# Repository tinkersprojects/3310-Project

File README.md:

# 3310 Project
The goal of the project is to make a working Nokia 3310 that works with today's tech. The device will be as similar as the original including the screen and body (case). It is unknown what process will be in the finished device but the first will have an ESP32. The ESP32 has both Bluetooth and WiFi which will be used to connect to a smartphone as an extension accessory. 

From the Nokia 3310, the user will be able to make/receive calls and SMS/text messages as well as play original games and all other good features. Additional features like social networking will come later. A micro USB port is used for charging, programming and debugging of the ESP32.

This first prototype is very basic to see which areas would need the most amount of work and to see if this project is worth continuing. There are features missing and features that will not be apart of the device. This prototype will look mostly at getting the LCD, keypad and Bluetooth/WiFi working.

**Get involved, [contact me](https://tinkersprojects.com/contact-me/)**

**See my other projects, [https://tinkersprojects.com/](https://tinkersprojects.com/)**

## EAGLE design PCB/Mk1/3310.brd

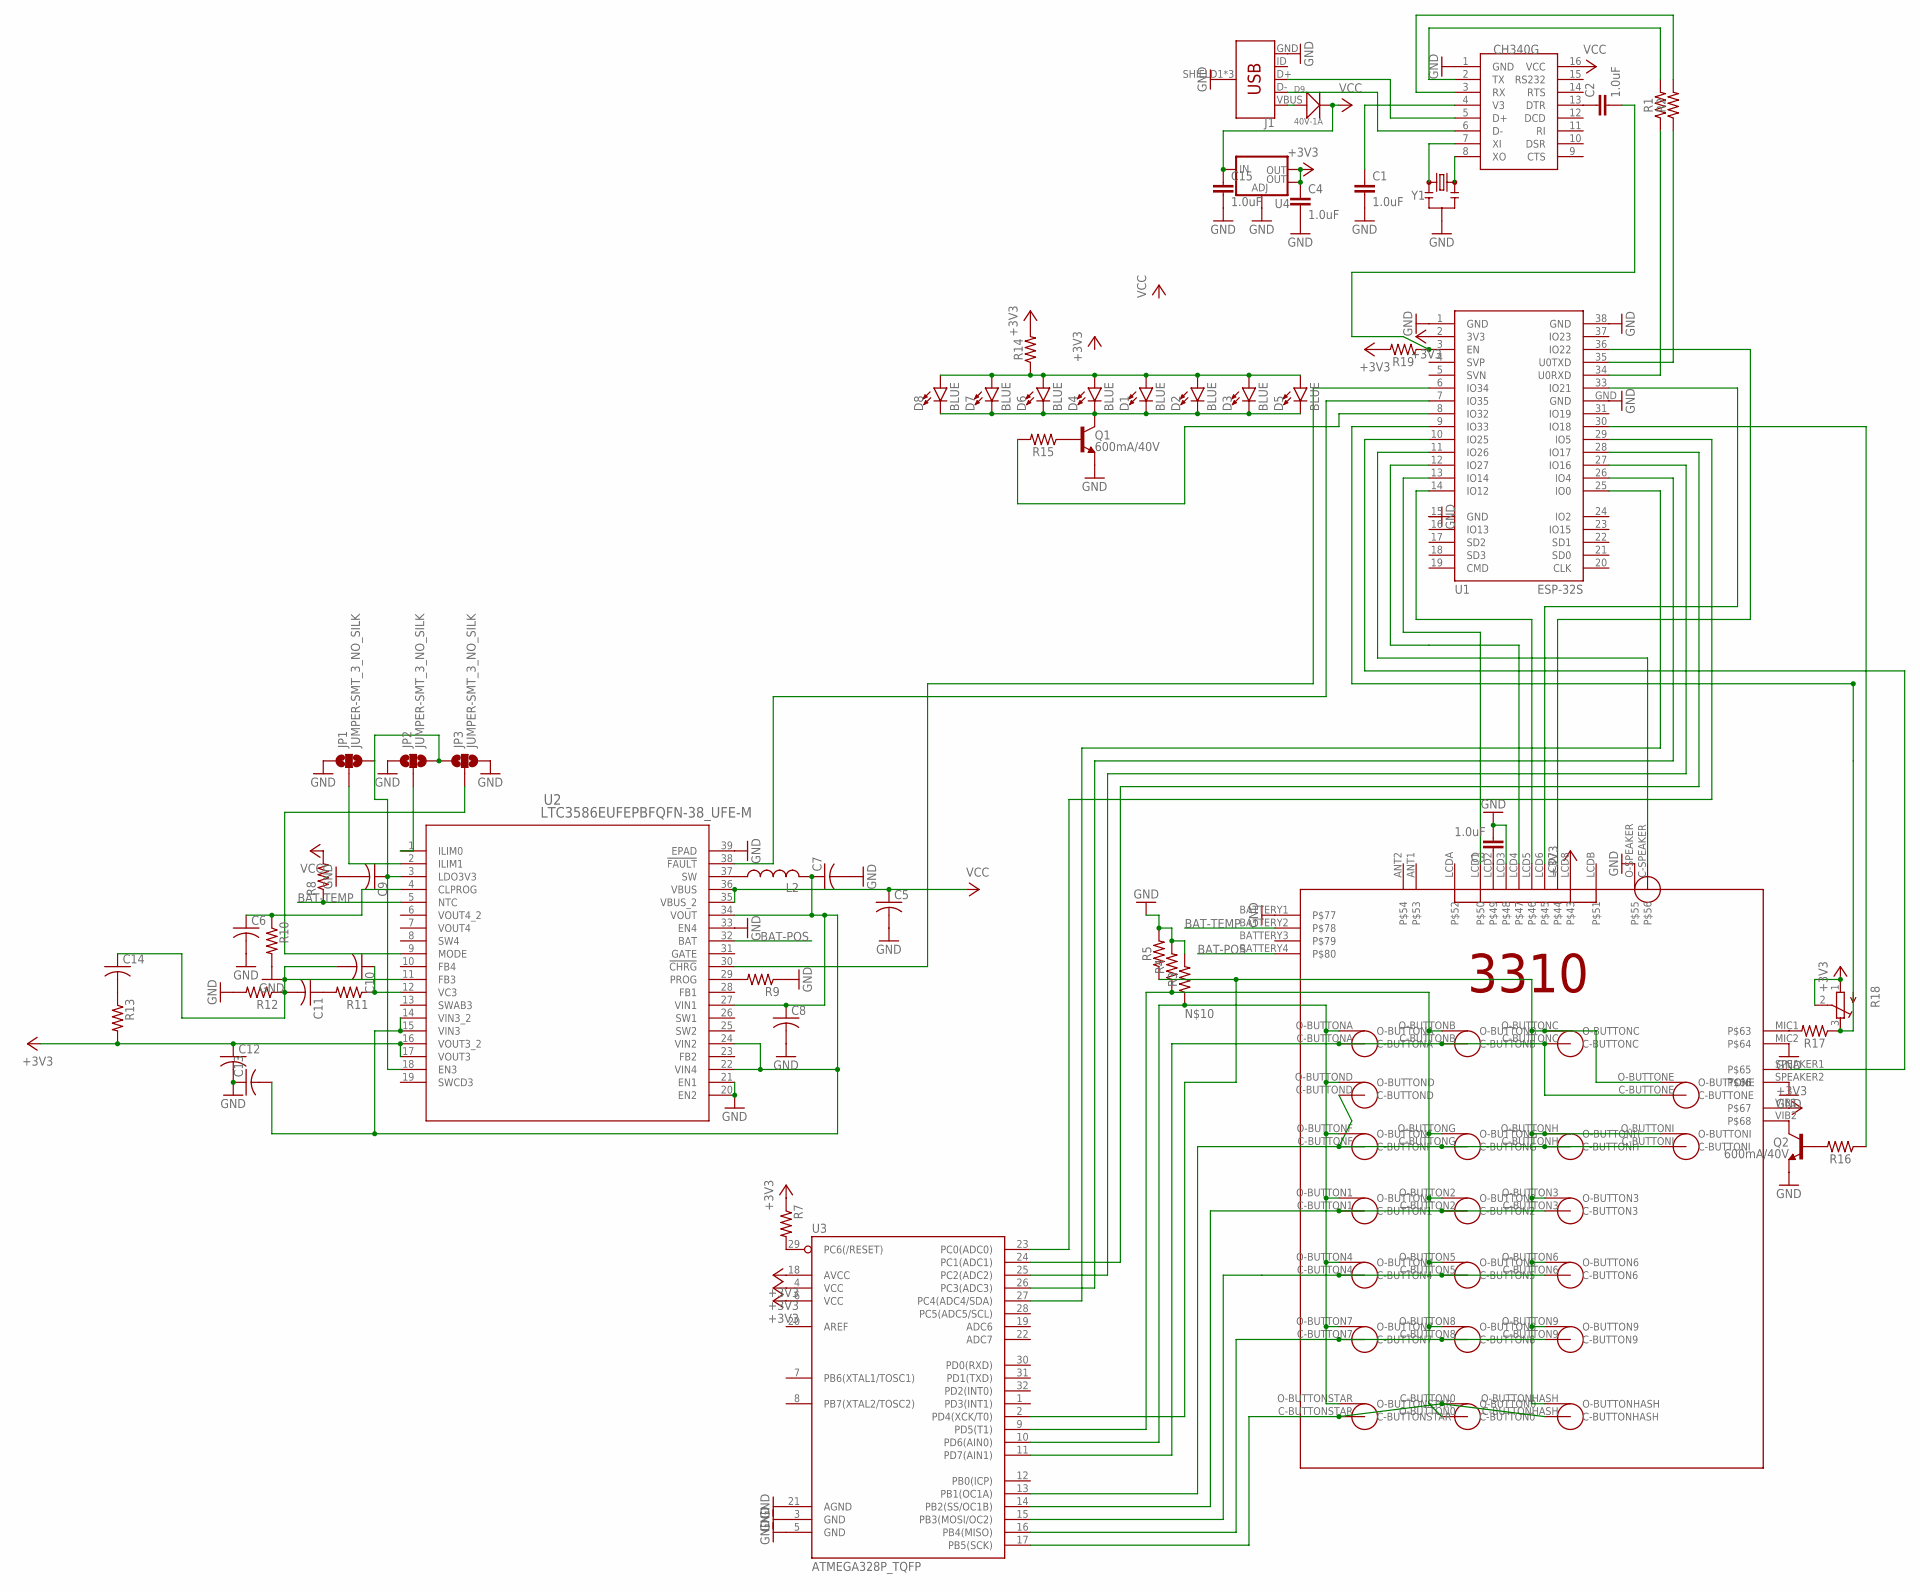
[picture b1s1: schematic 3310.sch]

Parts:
C1, C2, C3, C4, C15: 1.0uF; 0805
C5, C6, C7, C8, C9, C10, C11, C12, C13, C14: C-USC0805K; C0805K
D1, D2, D3, D4, D5, D6, D7, D8: BLUE; LED-1206
D9: 40V-1A; DO-214AC
J1: USB_MICRO-BREDUCED_PASTE; USB-B-MICRO-SMD_RED_PASTE
JP1, JP2, JP3: JUMPER-SMT_3_NO_SILK; SMT-JUMPER_3_NO_SILK
L2: L-USL3216C; L3216C
Q1, Q2: 600mA/40V; SOT23-3
R1, R2, R3, R4, R5, R14, R15, R16, R17, R19: 0805
R7, R8, R9, R10, R11, R12, R13: R-US_R0805; R0805
R18: R-TRIMM3103; RTRIM3103
U1: ESP-32S
U2: LTC3586EUFEPBFQFN-38_UFE-M; QFN-38_UFE-M
U3: ATMEGA328P_TQFP; TQFP32-08
U4: V_REG_LM1117SOT223; SOT223
U$1: 3310NOJACKANDSIM
U$2: CH340G; SOIC16
Y1: RESONATORSMD-3.2X1.3; RESONATOR-SMD-3.2X1.3

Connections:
+3V3: C4.1, C12.1, R7.1, R13.2, R14.2, R18.1 (A), R18.2 (S), R19.2, U1.2 (3V3), U2.16 (VOUT3_2), U2.17 (VOUT3), U3.4 (VCC), U3.6 (VCC), U3.18 (AVCC), U4.2 (OUT), U4.4 (OUT), U$1.LCD8, U$1.VIB1
BAT-POS: U2.32 (BAT), U$1.BATTERY4
BAT-TEMP: R8.1, U2.5 (NTC), U$1.BATTERY2
GND: C1.2, C3.2, C4.2, C5.2, C6.2, C7.2, C8.2, C9.2, C12.2, C13.1, C15.2, J1.GND, J1.SHIELD1 (SHIELD), J1.SHIELD2 (SHIELD), J1.SHIELD3 (SHIELD), JP1.1, JP2.1, JP3.3, Q1.2 (E), Q2.2 (E), R3.2, R4.2, R5.2, R9.1, R10.2, R12.2, U1.1 (GND), U1.15 (GND), U1.38 (GND), U1.GND, U2.20 (EN2), U2.21 (EN1), U2.33 (EN4), U2.39 (EPAD), U3.3 (GND), U3.5 (GND), U3.21 (AGND), U4.1 (ADJ), U$1.BATTERY1, U$1.LCD3, U$1.MIC2, U$1.O-SPEAKER, U$1.SPEAKER2, U$2.1 (GND), Y1.2
unnamed: J1.D-, U$2.6 (D-)
unnamed: D1.A, D2.A, D3.A, D4.A, D5.A, D6.A, D7.A, D8.A, R14.1
unnamed: U3.17 (PB5(SCK)), U$1.C-BUTTON0 (O-BUTTON0), U$1.C-BUTTONHASH, U$1.C-BUTTONSTAR
unnamed: U3.16 (PB4(MISO)), U$1.C-BUTTON7, U$1.C-BUTTON8, U$1.C-BUTTON9
unnamed: U3.15 (PB3(MOSI/OC2)), U$1.C-BUTTON4, U$1.C-BUTTON5, U$1.C-BUTTON6
unnamed: U3.14 (PB2(SS/OC1B)), U$1.C-BUTTON1, U$1.C-BUTTON2, U$1.C-BUTTON3
unnamed: U3.13 (PB1(OC1A)), U$1.C-BUTTOND, U$1.C-BUTTONF, U$1.C-BUTTONG, U$1.C-BUTTONH, U$1.C-BUTTONI
unnamed: R5.1, U3.2 (PD4(XCK/T0)), U$1.O-BUTTON3, U$1.O-BUTTON6, U$1.O-BUTTON9, U$1.O-BUTTONC, U$1.O-BUTTONE, U$1.O-BUTTONH, U$1.O-BUTTONHASH, U$1.O-BUTTONI
unnamed: U3.11 (PD7(AIN1)), U$1.C-BUTTONA, U$1.C-BUTTONB, U$1.C-BUTTONC, U$1.C-BUTTONE
unnamed: R3.1, U3.10 (PD6(AIN0)), U$1.O-BUTTON1, U$1.O-BUTTON4, U$1.O-BUTTON7, U$1.O-BUTTONA, U$1.O-BUTTOND, U$1.O-BUTTONF, U$1.O-BUTTONSTAR
unnamed: R4.1, U3.9 (PD5(T1)), U$1.O-BUTTON0 (C-BUTTON0), U$1.O-BUTTON2, U$1.O-BUTTON5, U$1.O-BUTTON8, U$1.O-BUTTONB, U$1.O-BUTTONG
unnamed: J1.D+, U$2.5 (D+)
unnamed: D9.1 (+), J1.VBUS
unnamed: U$2.8 (XO), Y1.3
unnamed: U$2.7 (XI), Y1.1
unnamed: C1.1, U$2.4 (V3)
unnamed: C2.1, U$2.13 (DTR)
unnamed: C2.2, R19.1, U1.3 (EN)
unnamed: R1.2, U$2.2 (TX)
unnamed: R2.2, U$2.3 (RX)
unnamed: R1.1, U1.34 (U0RXD)
unnamed: R2.1, U1.35 (U0TXD)
unnamed: U1.14 (IO12), U$1.LCD5
unnamed: C3.1, U$1.LCD2
unnamed: U1.13 (IO14), U$1.LCD1
unnamed: U1.12 (IO27), U$1.LCD4
unnamed: U1.36 (IO22), U$1.LCD7
unnamed: U1.33 (IO21), U$1.LCD6
unnamed: R9.2, U2.29 (PROG)
unnamed: C6.1, R10.1, U2.4 (CLPROG)
unnamed: L2.1, U2.37 (SW)
unnamed: C14.2, R13.1
unnamed: C9.1, JP1.3, JP2.3, JP3.1, U2.3 (LDO3V3), U2.18 (EN3)
unnamed: U1.7 (IO35), U2.38 (!FAULT)
unnamed: C10.1, R11.1, U2.12 (VC3)
unnamed: C11.1, R11.2
unnamed: C10.2, C11.2, C14.1, R12.1, U2.11 (FB3)
unnamed: JP2.2, U2.1 (ILIM0)
unnamed: C7.1, C8.1, C13.2, L2.2, U2.14 (VIN3_2), U2.15 (VIN3), U2.22 (VIN4), U2.24 (VIN2), U2.27 (VIN1), U2.34 (VOUT)
unnamed: JP1.2, U2.2 (ILIM1)
unnamed: U1.6 (IO34), U2.30 (!CHRG)
unnamed: U1.29 (IO5), U3.23 (PC0(ADC0))
unnamed: U1.28 (IO17), U3.24 (PC1(ADC1))
unnamed: R7.2, U3.29 (PC6(/RESET))
unnamed: U1.27 (IO16), U3.25 (PC2(ADC2))
unnamed: U1.26 (IO4), U3.26 (PC3(ADC3))
unnamed: U1.25 (IO0), U3.27 (PC4(ADC4/SDA))
unnamed: D1.C, D2.C, D3.C, D4.C, D5.C, D6.C, D7.C, D8.C, Q1.3 (C)
unnamed: Q1.1 (B), R15.1
unnamed: R15.2, U1.8 (IO32)
unnamed: Q2.3 (C), U$1.VIB2
unnamed: Q2.1 (B), R16.2
unnamed: R16.1, U1.30 (IO18)
unnamed: JP3.2, U2.9 (MODE)
unnamed: R17.2, U$1.MIC1
unnamed: R17.1, R18.3 (E), U1.9 (IO33)
unnamed: U1.11 (IO26), U$1.C-SPEAKER
unnamed: U1.10 (IO25), U$1.SPEAKER1
VCC: C5.1, C15.1, D9.2 (-), R8.2, U2.35 (VBUS_2), U2.36 (VBUS), U4.3 (IN), U$2.16 (VCC)

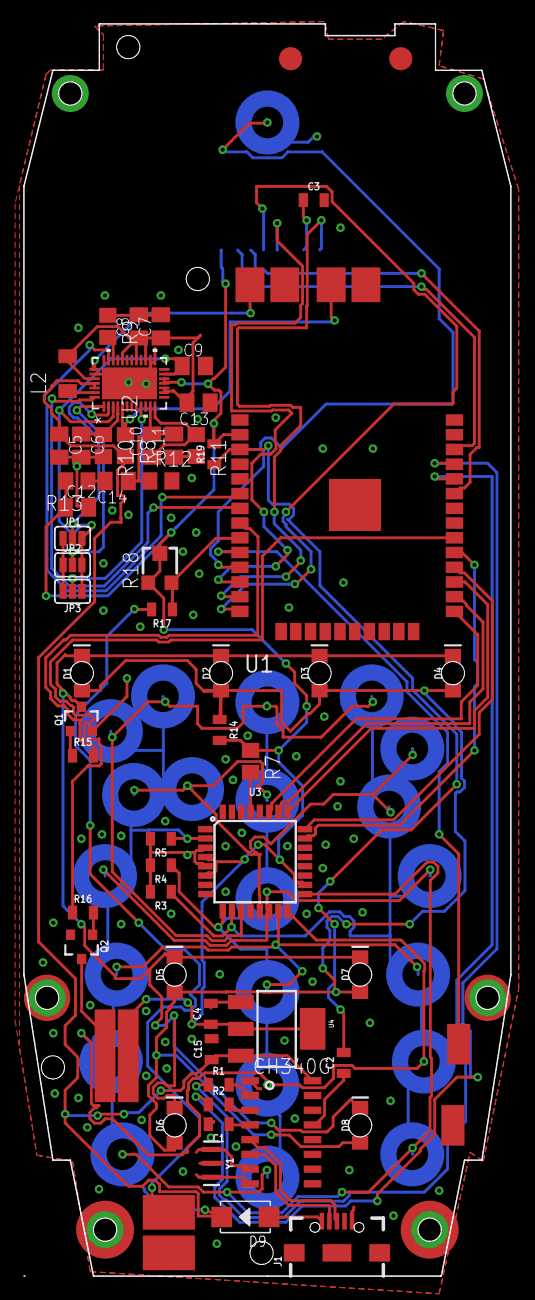
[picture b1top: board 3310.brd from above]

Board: 2 copper layers, 42.0 x 108.0 mm, 56 parts (1 on the bottom side), 63 nets.

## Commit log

2018-10-10 Rename 3310.sch to PCB/Mk1/3310.sch
2018-10-10 Rename 3310.brd to PCB/Mk1/3310.brd
2018-10-10 Rename 3310.lbr to library files/3310.lbr
2018-10-10 Rename 3310.lbr to Eagle Library/3310.lbr

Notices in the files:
parts and their libraries:
esp32: Creative Commons Attribution-ShareAlike 4.0 International
SparkFun-LED: Licensing: Creative Commons ShareAlike 4.0 International - https://creativecommons.org/licenses/by-sa/4.0
